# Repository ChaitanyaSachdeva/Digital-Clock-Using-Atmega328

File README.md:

# Digital-Clock-Using-Atmega328

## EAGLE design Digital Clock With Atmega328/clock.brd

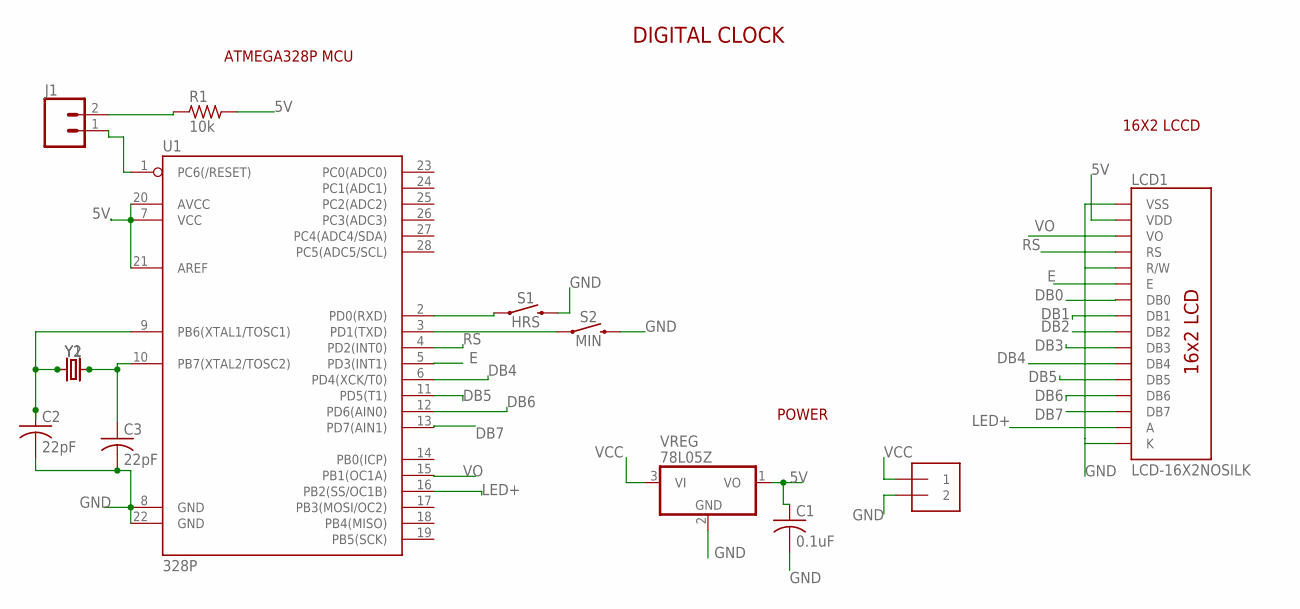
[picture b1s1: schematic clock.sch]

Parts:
C1: 0.1uF; C1206
C2, C3: 22pF; C1206
J1: CONN_02; 1X02
LCD1: LCD-16X2NOSILK; LCD-16X2_NOSILK
POWER: 1X2-3.5MM
R1: 10k; R1206
S1: HRS; TACTILE_SWITCH_PTH_6.0MM
S2: MIN; TACTILE_SWITCH_PTH_6.0MM
U1: 328P; DIP28
VREG: 78L05Z; TO92
Y1, Y2: CRYSTALPTH-HC49US; HC49US

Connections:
5V: C1.1, LCD1.2 (VDD), R1.2, U1.7 (VCC), U1.20 (AVCC), U1.21 (AREF), VREG.1 (VO)
DB0: LCD1.7 (DB0)
DB1: LCD1.8 (DB1)
DB2: LCD1.9 (DB2)
DB3: LCD1.10 (DB3)
DB4: LCD1.11 (DB4), U1.6 (PD4(XCK/T0))
DB5: LCD1.12 (DB5), U1.11 (PD5(T1))
DB6: LCD1.13 (DB6), U1.12 (PD6(AIN0))
DB7: LCD1.14 (DB7), U1.13 (PD7(AIN1))
E: LCD1.6 (E), U1.5 (PD3(INT1))
GND: C1.2, C2.1, C2.2, C3.2, LCD1.16 (K), POWER.2, S1.3 (2), S2.3 (2), U1.8 (GND), U1.9 (PB6(XTAL1/TOSC1)), U1.22 (GND), VREG.2 (GND), Y1.1, Y2.1
LED+: LCD1.15 (A), U1.16 (PB2(SS/OC1B))
unnamed: LCD1.1 (VSS), LCD1.5 (R/W)
unnamed: S1.1, U1.2 (PD0(RXD))
unnamed: S2.1, U1.3 (PD1(TXD))
unnamed: J1.1, U1.1 (PC6(/RESET))
unnamed: J1.2, R1.1
unnamed: C3.1, U1.10 (PB7(XTAL2/TOSC2)), Y1.2, Y2.2
RS: LCD1.4 (RS), U1.4 (PD2(INT0))
VCC: POWER.1, VREG.3 (VI)
VO: LCD1.3 (VO), U1.15 (PB1(OC1A))

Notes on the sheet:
ATMEGA328P MCU
POWER
16X2 LCCD
DIGITAL CLOCK

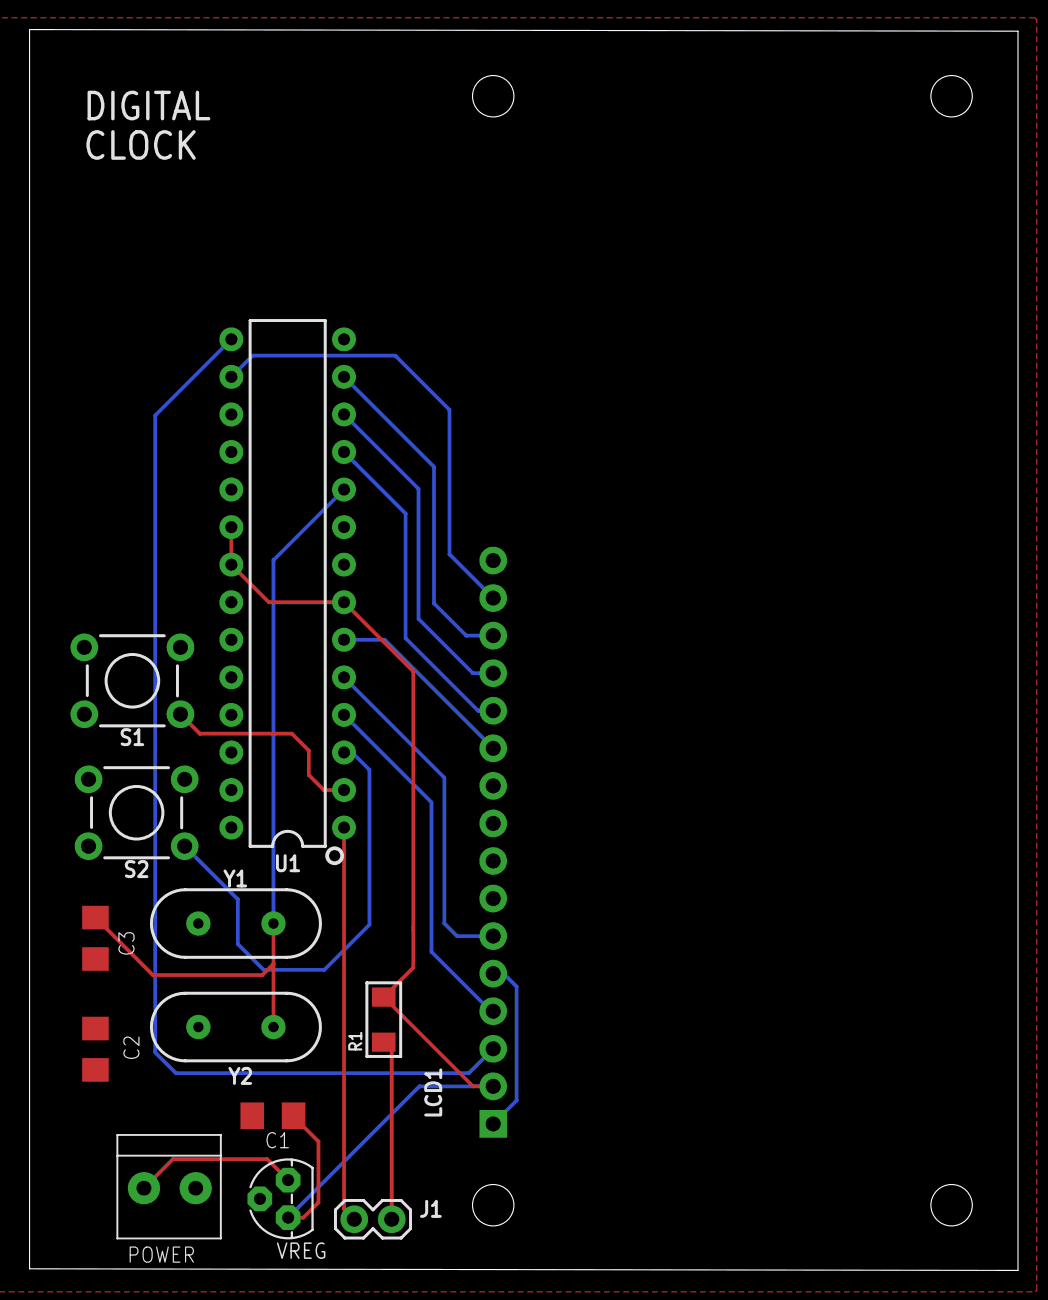
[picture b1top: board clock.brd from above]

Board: 2 copper layers, 66.8 x 83.9 mm, 13 parts (0 on the bottom side), 17 nets.

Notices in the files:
parts and their libraries:
SparkFun-Displays: Licensing: Creative Commons ShareAlike 4.0 International - https://creativecommons.org/licenses/by-sa/4.0
rc-master-smd: Copyright (C) 2007, Bob Starr
